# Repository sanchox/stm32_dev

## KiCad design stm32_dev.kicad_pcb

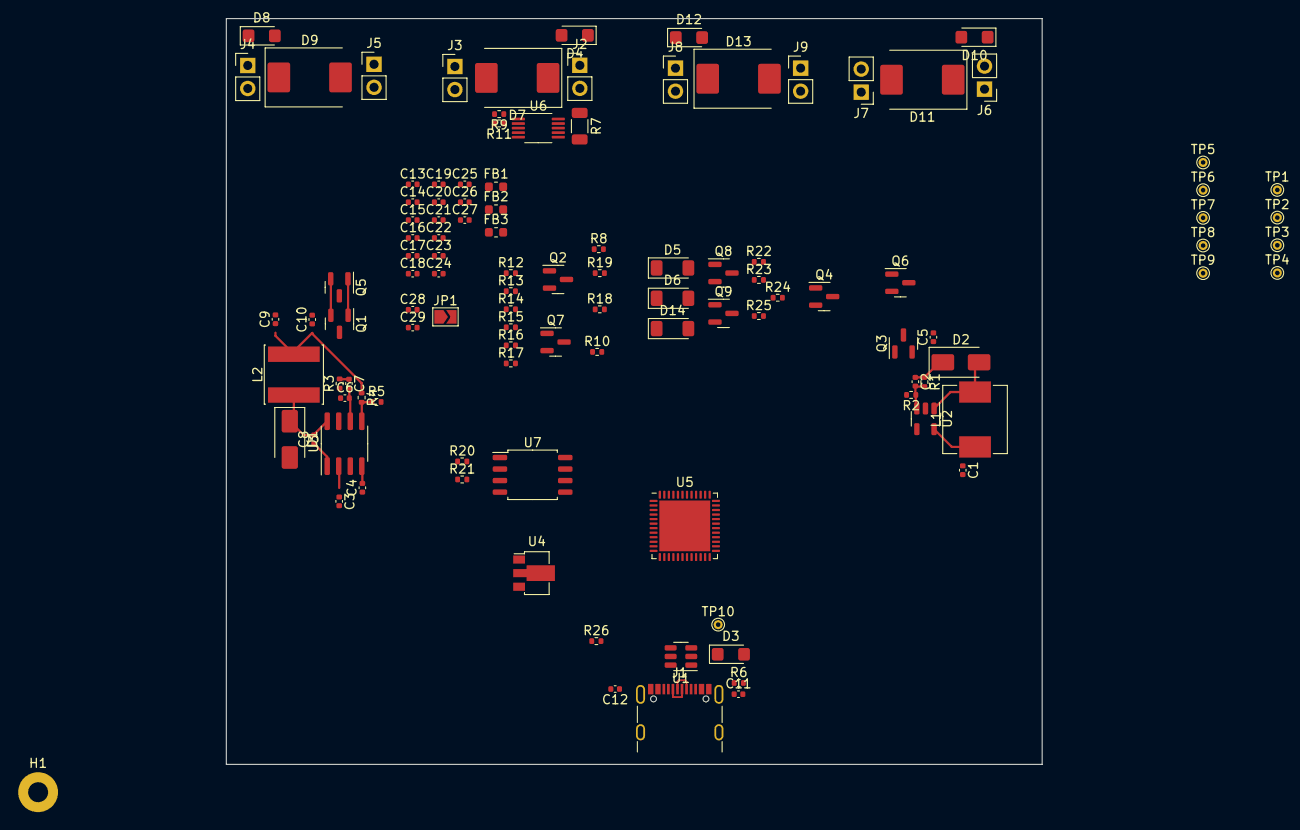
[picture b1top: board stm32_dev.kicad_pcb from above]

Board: 4 copper layers, 89.9 x 82.2 mm, 111 parts (0 on the bottom side), 48 nets.

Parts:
C1: 4.7uF; C_0402_1005Metric
C2: 22pF; C_0402_1005Metric
C3: 22uF; C_0402_1005Metric
C4: 10nF; C_0402_1005Metric
C5: 1uF; C_0402_1005Metric
C6: 10pF; C_0402_1005Metric
C7: 6.8nF; C_0402_1005Metric
C8, C16, C18, C22, C23, C24, C26, C27, C29: 100n; C_0402_1005Metric
C9, C10: 47uF; C_0402_1005Metric
C11, C12: DNP; C_0402_1005Metric
C13, C14: 22u; C_0402_1005Metric
C15, C19, C20, C21: 10u; C_0402_1005Metric
C17, C25, C28: 1u; C_0402_1005Metric
D1, D2: 40V 3A; D_SMA
D3, D4, D8, D10, D12: SMF30A; D_SMF
D5, D6, D14: 12V; D_MiniMELF
D7, D9, D11, D13: 40V 5A; D_SMC
FB1, FB2, FB3: 600 Ohm; L_0603_1608Metric
H1: MountingHole_Pad; MountingHole_2.2mm_M2_Pad
J1: USB_C_Receptacle_USB2.0; USB_C_Receptacle_GCT_USB4105-xx-A_16P_TopMnt_Horizontal
J2, J3, J4, J5, J6, J7, J8, J9: Conn_01x02; PinHeader_1x02_P2.54mm_Vertical
JP1: SolderJumper_2_Open; SolderJumper-2_P1.3mm_Open_TrianglePad1.0x1.5mm
L1: 10uH; L_Sunlord_MWSA0603S
L2: 15uH; L_Sunlord_SWPA6045S
Q1, Q3, Q4, Q5, Q6, Q9: AO3401A; SOT-23
Q2, Q7, Q8: 2N7002; SOT-23
R1: 2.2M; R_0402_1005Metric
R2: 200k; R_0402_1005Metric
R3: 2.7k; R_0402_1005Metric
R4, R8, R10, R12, R13, R23, R24: 10k; R_0402_1005Metric
R5: 3.3k; R_0402_1005Metric
R6, R9, R11, R20, R21, R26: 0; R_0402_1005Metric
R7: 0.1; R_1206_3216Metric
R14, R15, R25: 100k; R_0402_1005Metric
R16, R17, R22: 33; R_0402_1005Metric
R18, R19: 4.7k; R_0402_1005Metric
TP1, TP2, TP3, TP4, TP5, TP6, TP7, TP8, TP9, TP10: TestPoint; TestPoint_THTPad_D1.0mm_Drill0.5mm
U1: SRV05-4; SOT-23-6
U2: TPS61040DBV; SOT-23-5
U3: TPS54331D; SOIC-8_3.9x4.9mm_P1.27mm
U4: HT7533-1; SOT-89-3
U5: STM32G431CBUx; QFN-48-1EP_7x7mm_P0.5mm_EP5.6x5.6mm
U6: INA226; VSSOP-10_3x3mm_P0.5mm
U7: W25Q128JVS; SOIC-8_5.23x5.23mm_P1.27mm

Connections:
+3V3: C15.1, C16.1, FB1.2, FB3.2, U4.3 (VOUT)
BOOST_EN: R19.1, U2.4 (EN)
BOOST_IN: C1.1, L1.1, U2.5 (VIN)
BOOST_OUT: C2.1, C5.1, D2.1 (K), D10.1 (A1), D11.1 (K), J6.1, J6.2, Q3.3 (D), R1.1
BUCK_EN: R18.1, U3.3 (EN)
BUCK_IN: C3.1, U3.2 (VIN)
BUCK_OUT: C9.1, C10.1, D8.1 (A1), D9.1 (K), J4.1, J4.2, L2.2, Q1.3 (D), R4.1
GND: C1.2, C3.2, C4.1, C5.2, C6.1, C9.2, C10.2, C11.2, C12.2, C13.2, C14.2, C15.2, C16.2, C17.2, C18.2, C19.2, C20.2, C21.2, C22.2, C23.2, C24.2, C25.2, C26.2, C27.2, C28.2, C29.2, D1.2 (A), D3.2 (A2), D4.2 (A2), D7.2 (A), D8.2 (A2), D9.2 (A), D10.2 (A2), D11.2 (A), D12.2 (A2), D13.2 (A), J1.A1 (GND), J1.A12 (GND), J1.B1 (GND), J1.B12 (GND), J3.1, J3.2, J5.1, J5.2, J7.1, J7.2, J9.1, J9.2, Q2.2 (S), Q7.2 (S), Q8.2 (S), R2.2, R3.2, R5.2, R6.2, R8.1, R9.2, R10.1, R11.2, R18.2, R19.2, R23.1, U1.2 (VN), U2.2 (GND), U3.7 (GND), U4.1 (GND), U5.49 (VSS), U6.7 (GND), U7.4 (GND)
unnamed: C27.1, R26.2
unnamed: C7.2, R3.1
unnamed: C17.1, C26.1, FB3.1
unnamed: C8.2, D1.1 (K), L2.1, U3.8 (PH)
unnamed: D2.2 (A), L1.2, U2.1 (SW)
unnamed: D4.1 (A1), D7.1 (K), J2.1, J2.2, R7.1, U6.9 (Vin-)
unnamed: D5.2 (A), Q3.1 (G), Q6.1 (G), R12.2, R14.1
unnamed: D5.1 (K), Q3.2 (S), Q6.2 (S), R12.1
unnamed: D6.2 (A), Q1.1 (G), Q5.1 (G), R13.2, R15.1
unnamed: D6.1 (K), Q1.2 (S), Q5.2 (S), R13.1
unnamed: D14.2 (A), Q4.1 (G), Q9.1 (G), R24.2, R25.1
unnamed: D14.1 (K), Q4.2 (S), Q9.2 (S), R24.1
unnamed: C11.1, C12.1, J1.S1 (SHIELD), R6.1
unnamed: C28.1, C29.1, JP1.2 (B)
unnamed: Q2.3 (D), R14.2
unnamed: Q2.1 (G), R8.2, R17.2
unnamed: Q5.3 (D), Q6.3 (D), Q9.3 (D), R7.2, U6.8 (Vbus), U6.10 (Vin+)
unnamed: Q7.3 (D), R15.2
unnamed: Q7.1 (G), R10.2, R16.2
unnamed: Q8.3 (D), R25.2
unnamed: Q8.1 (G), R22.2, R23.2
unnamed: C2.2, R1.2, R2.1, U2.3 (FB)
unnamed: C8.1, U3.1 (BOOT)
unnamed: C6.2, C7.1, U3.6 (COMP)
unnamed: C4.2, U3.4 (SS)
unnamed: R4.2, R5.1, U3.5 (VSENSE)
unnamed: TP2.1, U5.19 (PB2)
unnamed: TP1.1, U5.2 (PC13)
unnamed: TP3.1, U5.7 (PG10)
unnamed: R11.1, U6.2 (A0)
unnamed: R9.1, U6.1 (A1)
unnamed: R21.2, U7.3 (IO2)
unnamed: R20.2, U7.7 (IO3)
USB_CC1: J1.A5 (CC1), U1.4 (IO3)
USB_CC2: J1.B5 (CC2), U1.3 (IO4)
USB_D+: J1.A6 (D+), J1.B6 (D+), U1.6 (IO2)
USB_D-: J1.A7 (D-), J1.B7 (D-), U1.1 (IO1)
VBUS: C13.1, C14.1, D3.1 (A1), D12.1 (A1), D13.1 (K), J1.A4 (VBUS), J1.A9 (VBUS), J1.B4 (VBUS), J1.B9 (VBUS), J8.1, J8.2, Q4.3 (D), TP10.1, U4.2 (VIN)
VDD: C19.1, C20.1, C21.1, C22.1, C23.1, C24.1, FB1.1, FB2.2, JP1.1 (A), R20.1, R21.1, R26.1, U5.23 (VDD), U5.35 (VDD), U5.48 (VDD), U7.8 (VCC)
VDDA: C18.1, C25.1, FB2.1, U5.21 (VDDA)

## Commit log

2023-03-20 Init commit
